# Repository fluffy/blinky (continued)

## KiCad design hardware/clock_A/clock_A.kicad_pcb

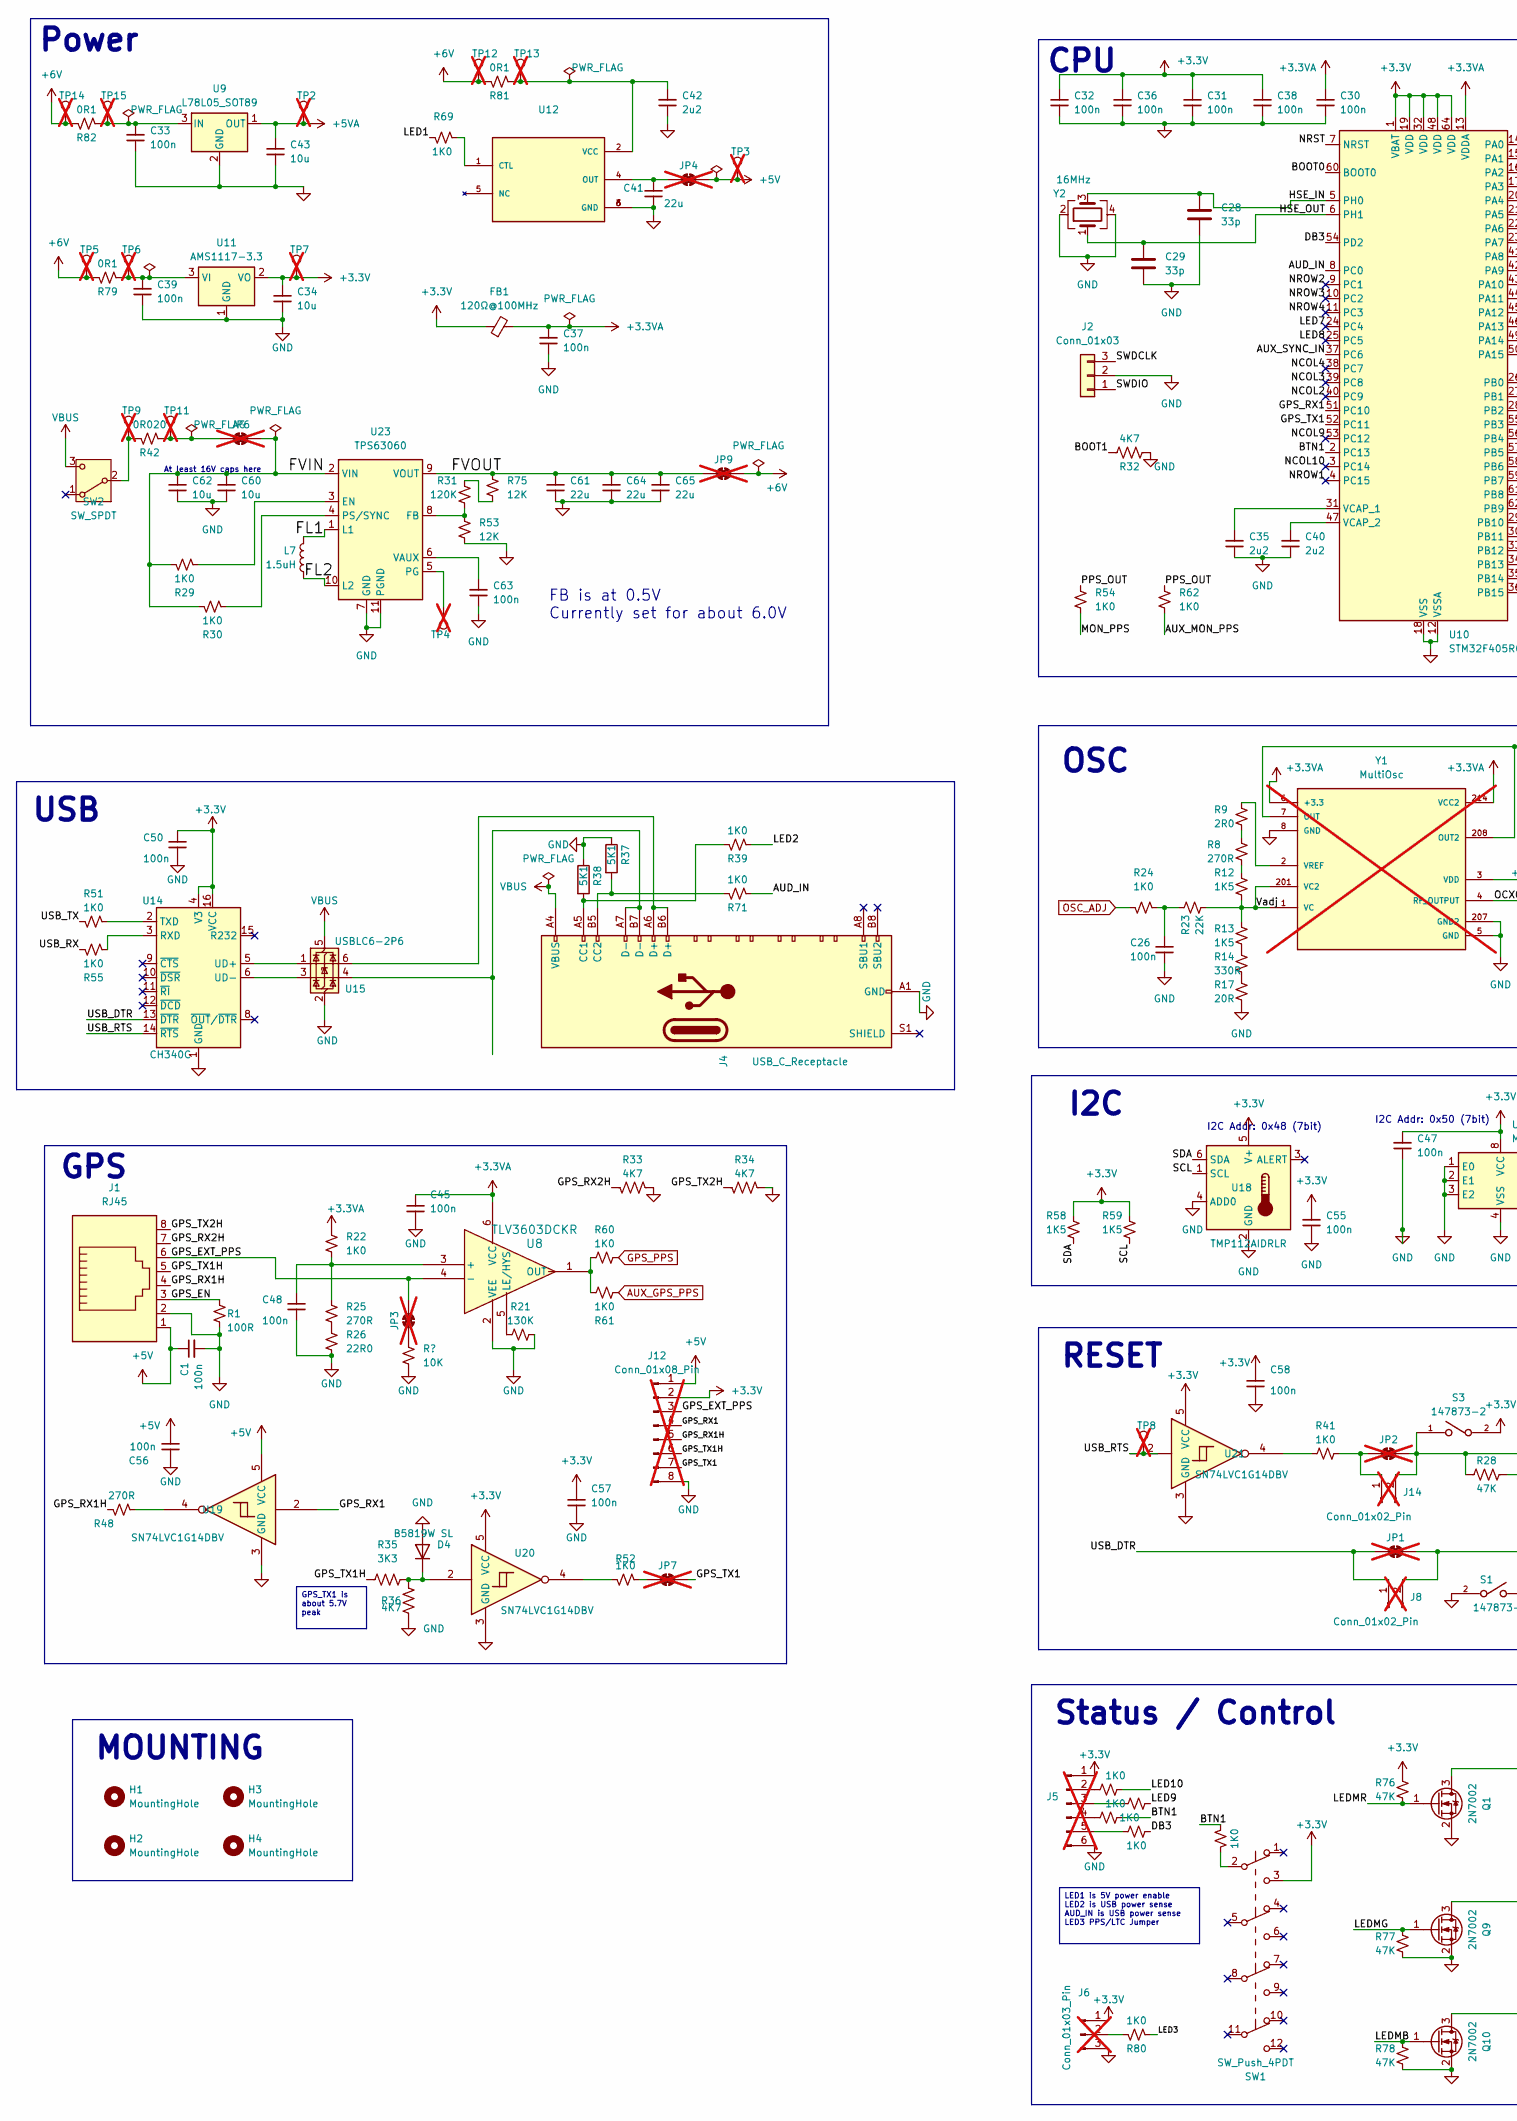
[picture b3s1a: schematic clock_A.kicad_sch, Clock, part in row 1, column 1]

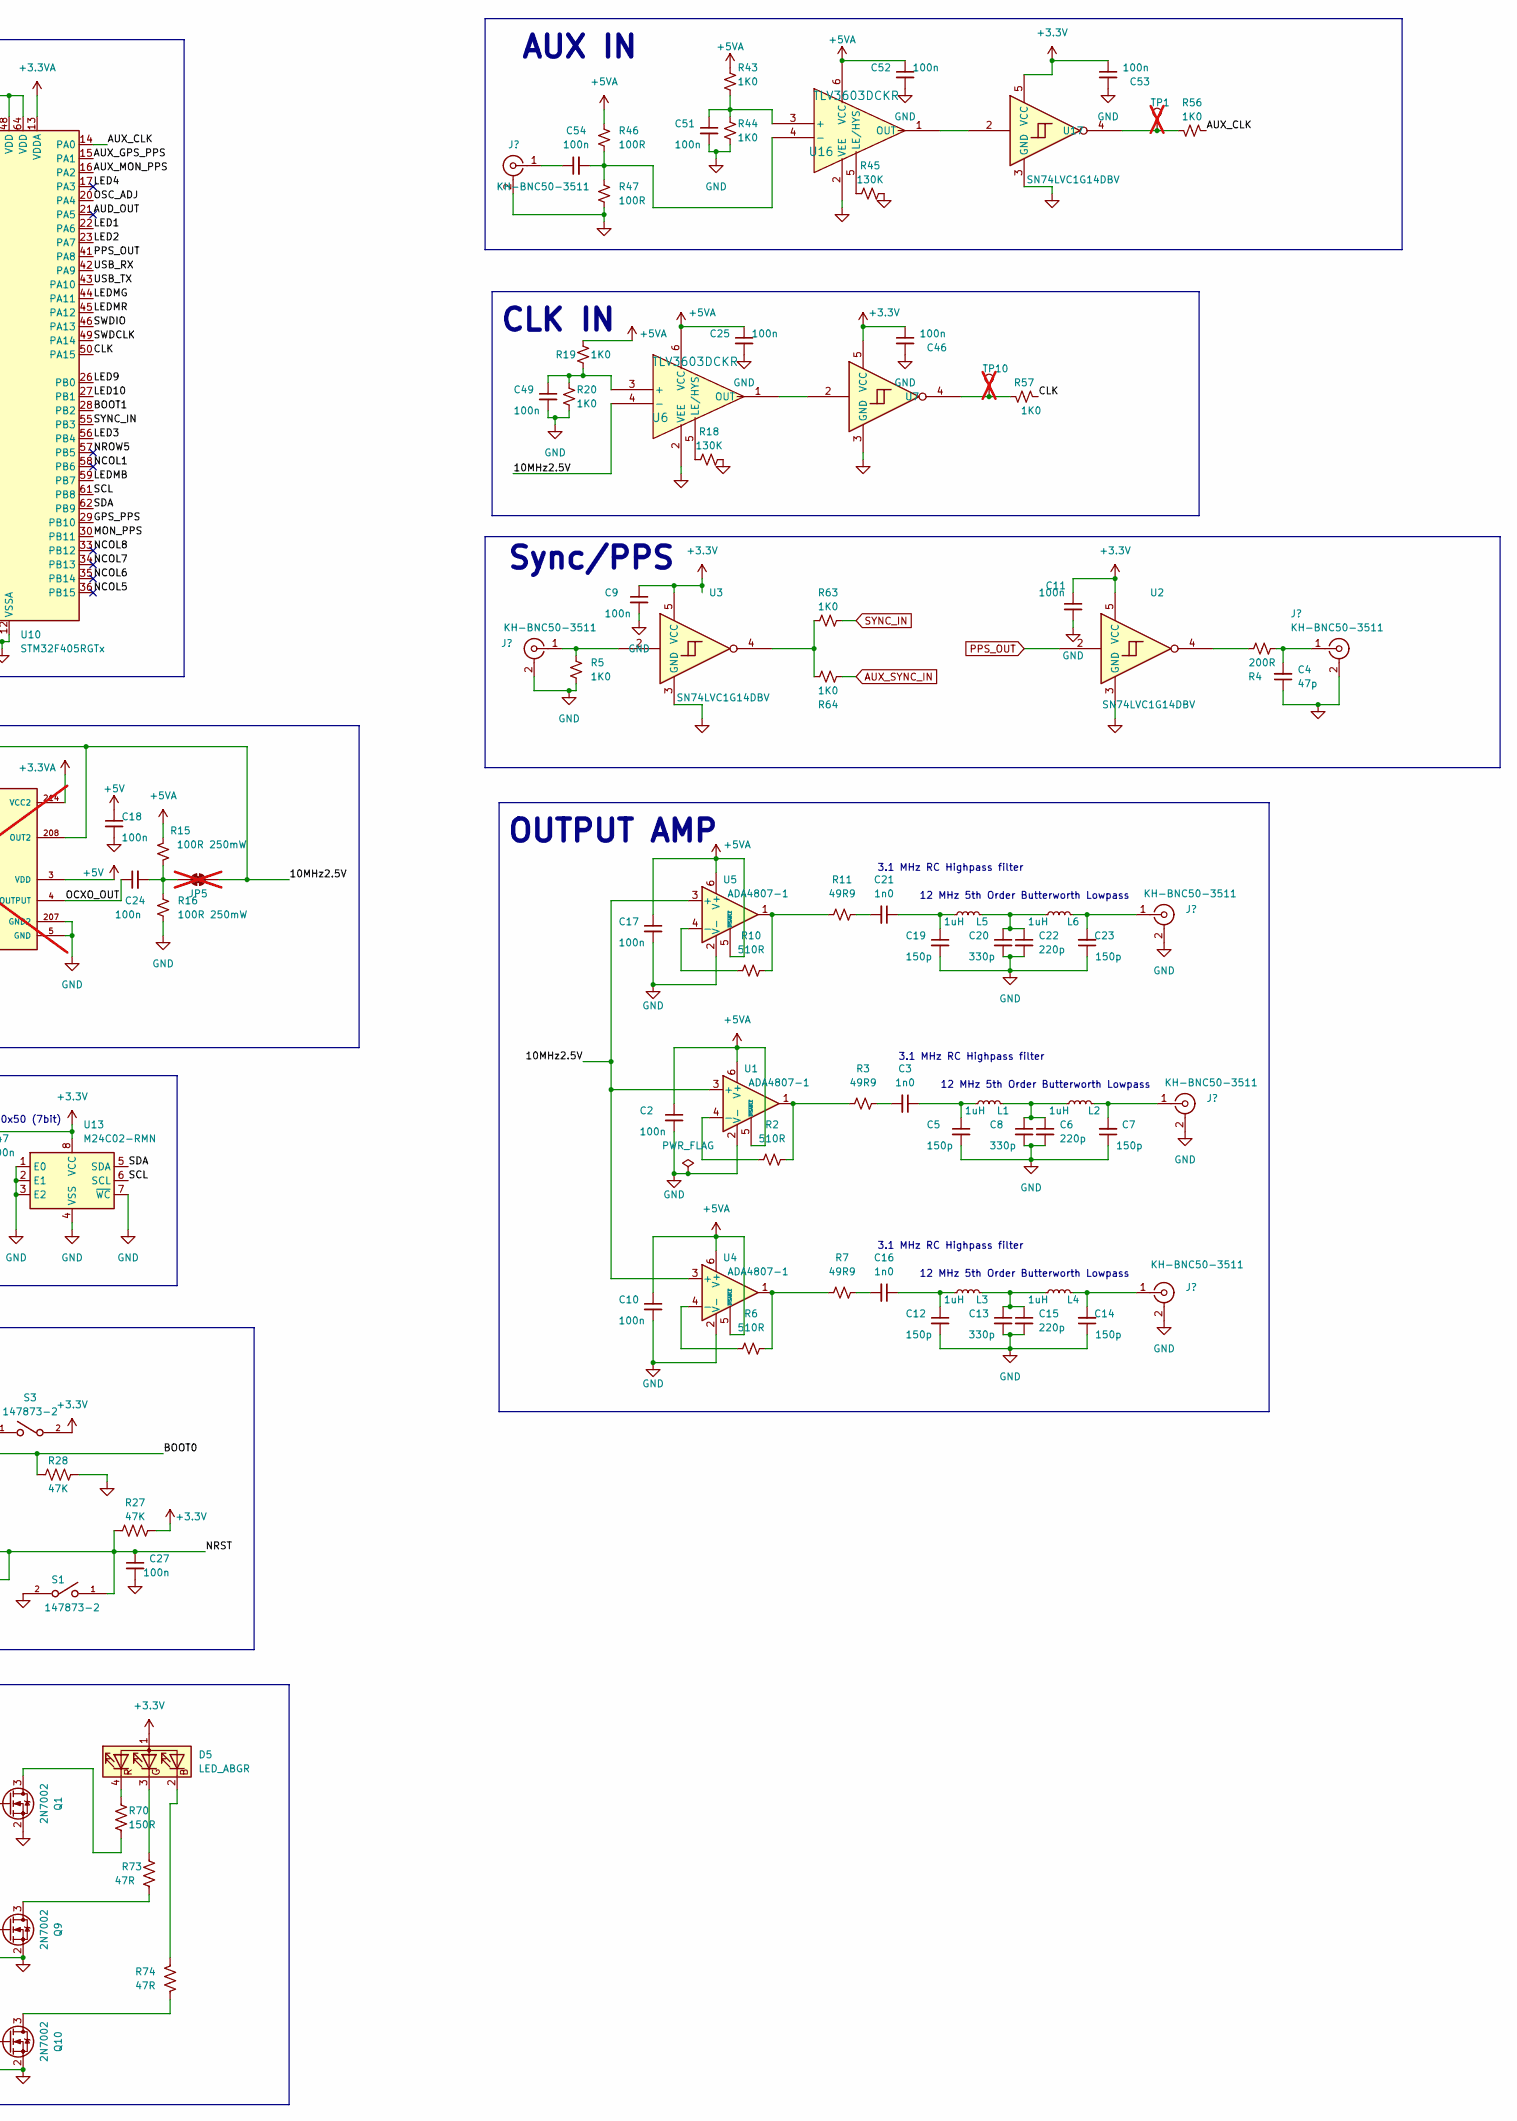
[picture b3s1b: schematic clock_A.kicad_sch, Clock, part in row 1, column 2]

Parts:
C1, C2, C9, C10, C11, C17, C18, C25, C26, C30, C31, C32, C33, C36, C38, C39, C45, C46, C47, C48, C49, C50, C51, C52, C53, C55, C56, C57, C58: 100n; C_0402_1005Metric; JLCPCB Part # C307331
C3, C16, C21: 1n0; C_0603_1608Metric; JLCPCB Part # C1588
C4: 47p; C_0603_1608Metric; JLCPCB Part # C1671
C5, C7, C12, C14, C19, C23: 150p; C_0603_1608Metric; JLCPCB Part # C1594
C6, C15, C22: 220p; C_0603_1608Metric; JLCPCB Part # C1603
C8, C13, C20: 330p; C_0603_1608Metric; JLCPCB Part # C1664
C24, C27, C37, C54, C63: 100n; C_0603_1608Metric; JLCPCB Part # C14663
C28, C29: 33p; C_0603_1608Metric; JLCPCB Part # C1663
C34, C43, C60, C62: 10u; C_0603_1608Metric; JLCPCB Part # C96446
C35, C40, C42: 2u2; C_0603_1608Metric; JLCPCB Part # C23630
C41, C61, C64, C65: 22u; C_0805_2012Metric; JLCPCB Part # C45783
D4: B5819W SL; D_SOD-123; JLCPCB Part # C8598
D5: LED_ABGR; LED_RGB_MHS110FRGBCT; MPN MHS110FRGBCT; JLCPCB Part # C496820
FB1: 120Ω@100MHz; R_0603_1608Metric; JLCPCB Part # C127301
H1, H2, H3, H4: MountingHole; MountingHole_2.2mm_M2
J1: RJ45; RJ45_Amphenol_RJHSE5380; JLCPCB Part # C464586
J2: Conn_01x03; JST_PH_S3B-PH-SM4-TB_1x03-1MP_P2.00mm_Horizontal; JLCPCB Part # C265101
J3, J7, J9, J10, J11, J13: KH-BNC50-3511; BNC_Amphenol_B6252HB-NPP3G-50_Horizontal-CJ; JLCPCB Part # C2837587
J4: USB_C_Receptacle; USB_C_Receptacle_HRO_TYPE-C-31-M-12; JLCPCB Part # C165948
J5: Conn_01x06_Pin; PinHeader_1x06_P2.54mm_Vertical; not fitted
J6: Conn_01x03_Pin; PinHeader_1x03_P2.54mm_Vertical; not fitted
J8, J14: Conn_01x02_Pin; PinHeader_1x02_P2.54mm_Vertical; not fitted
J12: Conn_01x08_Pin; PinHeader_1x08_P2.54mm_Vertical; not fitted
JP1, JP2, JP3, JP4, JP5, JP6, JP7, JP9: SolderJumper_2_Bridged; SolderJumper-2_P1.3mm_Bridged2Bar_RoundedPad1.0x1.5mm; not fitted
L1, L2, L3, L4, L5, L6: 1uH; L_0805_2012Metric; JLCPCB Part # C1042
L7: 1.5uH; L_Coilcraft_XAL4020-XXX; MPN XFL4020-152MEC; JLCPCB Part # C3033018
Q1, Q9, Q10: 2N7002; SOT-23; JLCPCB Part # C8545
R1, R46, R47: 100R; R_0603_1608Metric; JLCPCB Part # C22775
R2, R6, R10: 510R; R_0603_1608Metric; JLCPCB Part # C23193
R3, R7, R11: 49R9; R_0603_1608Metric; JLCPCB Part # C23185
R4: 200R; R_0603_1608Metric; JLCPCB Part # C8218
R5, R19, R20, R22, R24, R29, R30, R39, R41, R43, R44, R51, R52, R54, R55, R56, R57, R60, R61, R62, R63, R64, R65, R66, R67, R68, R69, R71, R72, R80: 1K0; R_0603_1608Metric; JLCPCB Part # C21190
R8, R25, R48: 270R; R_0603_1608Metric; JLCPCB Part # C22966
R9: 2R0; R_0603_1608Metric; JLCPCB Part # C22977
R12, R13, R58, R59: 1K5; R_0603_1608Metric; JLCPCB Part # C22843
R14: 330R; R_0603_1608Metric; JLCPCB Part # C23138
R15, R16: 100R 250mW; R_1206_3216Metric; JLCPCB Part # C17901
R17: 20R; R_0603_1608Metric; JLCPCB Part # C22950
R18, R21, R45: 130K; R_0603_1608Metric; JLCPCB Part # C22795
R23: 22K; R_0603_1608Metric; JLCPCB Part # C31850
R26: 22R0; R_0603_1608Metric; JLCPCB Part # C23345
R27, R28, R76, R77, R78: 47K; R_0603_1608Metric; JLCPCB Part # C25819
R31: 120K; R_0603_1608Metric; JLCPCB Part # C25808
R32, R33, R34, R36: 4K7; R_0603_1608Metric; JLCPCB Part # C23162
R35: 3K3; R_0603_1608Metric; JLCPCB Part # C22978
R37, R38: 5K1; R_0603_1608Metric; JLCPCB Part # C23186
R42: 0R020; R_1206_3216Metric; JLCPCB Part # C2765435
R50: 10K; R_0603_1608Metric; JLCPCB Part # C25804
R53, R75: 12K; R_0603_1608Metric; JLCPCB Part # C22790
R70: 150R; R_0603_1608Metric; JLCPCB Part # C22808
R73, R74: 47R; R_0603_1608Metric; JLCPCB Part # C23182
R79, R81, R82: 0R1; R_1206_3216Metric; JLCPCB Part # C25334
S1, S3: 147873-2; SW_147873-2; JLCPCB Part # C266189
SW1: SW_Push_4PDT; PBH4UOANAGX; JLCPCB Part # C273424
SW2: SW_SPDT; SW_E-Switch_EG1224_SPDT_Angled; JLCPCB Part # C273395
TP1, TP2, TP3, TP4, TP5, TP6, TP7, TP8, TP9, TP10, TP11, TP12, TP13, TP14, TP15: TestPoint_THTPad_D1.0mm_Drill0.5mm; not fitted
U1, U4, U5: ADA4807-1; SOT-23-6; JLCPCB Rotation Offset 90
U2, U3, U7, U17, U19, U20, U21: SN74LVC1G14DBV; SOT-23-5; JLCPCB Part # C133145
U6, U8, U16: TLV3603DCKR; SOT-363_SC-70-6; JLCPCB Part # C5213955
U9: L78L05_SOT89; SOT-89-3; JLCPCB Part # C71136
U10: STM32F405RGTx; LQFP-64_10x10mm_P0.5mm; JLCPCB Part # C15742
U11: AMS1117-3.3; SOT-223-3_TabPin2; JLCPCB Part # C6186
U12: BA50DD0WHFP-TR; DPAK172P1054X200-6N; PARTREV 003; JLCPCB Position Offset -1.5,0
U13: M24C02-RMN; SOIC-8_3.9x4.9mm_P1.27mm; JLCPCB Part # C83836
U14: CH340C; SOIC-16_3.9x9.9mm_P1.27mm; JLCPCB Part # C7464026
U15: USBLC6-2P6; SOT-666; JLCPCB Part # C2827693
U18: TMP112AIDRLR; SOT-563; JLCPCB Part # C28927
U23: TPS63060; Texas_S-PWSON-N10_ThermalVias-CJ; JLCPCB Part # C48567
Y1: MultiOsc; XTAL_Multi; not fitted
Y2: 16MHz; Crystal_SMD_3225-4Pin_3.2x2.5mm; JLCPCB Part # C13738

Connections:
+3.3V: C9.1, C11.1, C31.1, C32.1, C34.1, C36.1, C38.1, C46.1, C47.2, C50.1, C53.1, C55.2, C57.1, C58.1, D5.1 (A), FB1.1, J5.1, J6.1, J12.2, R27.1, R58.1, R59.1, R76.1, S3.2, SW1.3 (C), TP7.1, U2.5 (VCC), U3.5 (VCC), U7.5 (VCC), U10.1 (VBAT), U10.19 (VDD), U10.32 (VDD), U10.48 (VDD), U10.64 (VDD), U11.2 (VO), U13.8 (VCC), U14.4 (V3), U14.16 (VCC), U17.5 (VCC), U18.5 (V+), U20.5 (VCC), U21.5 (VCC)
+3.3VA: C30.1, C37.2, C45.1, FB1.2, R22.1, U8.6 (VCC), U10.13 (VDDA), Y1.6 (+3.3), Y1.214 (VCC2)
+5V: C1.1, C18.1, C56.1, J1.1, J12.1, JP4.2 (B), TP3.1, U19.5 (VCC), Y1.3 (VDD)
+5VA: C2.1, C10.1, C17.1, C25.1, C43.1, C52.1, R15.1, R19.1, R43.1, R46.1, TP2.1, U1.5 (~DISABLE), U1.6 (V+), U4.5 (~DISABLE), U4.6 (V+), U5.5 (~DISABLE), U5.6 (V+), U6.6 (VCC), U9.1 (OUT), U16.6 (VCC)
+6V: JP9.2 (B), R79.2, R81.2, R82.2, TP5.1, TP12.1, TP14.1
/10MHz2.5V: JP5.1 (A), U1.3 (+), U4.3 (+), U5.3 (+), U6.4 (-), Y1.7 (OUT), Y1.208 (OUT2)
/AUD_IN: R71.2, U10.8 (PC0)
/AUD_OUT: U10.21 (PA5)
/AUX_CLK: R56.1, U10.14 (PA0)
/AUX_MON_PPS: R62.2, U10.16 (PA2)
/BOOT0: J14.2, JP2.2 (B), R28.1, S3.1, U10.60 (BOOT0)
/BOOT1: R32.2, U10.28 (PB2)
/BTN1: R66.1, R72.2, U10.2 (PC13)
/CLK: R57.1, U10.50 (PA15)
/DB3: R68.1, U10.54 (PD2)
/FL1: L7.1, U23.1 (L1)
/FL2: L7.2, U23.10 (L2)
/FVIN: C60.1, C62.1, JP6.2 (B), R29.1, R30.1, U23.2 (VIN)
/FVOUT: C61.1, C64.1, C65.1, JP9.1 (A), R75.1, U23.9 (VOUT)
/GPS_EN: J1.3, R1.1
/GPS_EXT_PPS: J1.6, J12.3, JP3.2 (B), U8.4 (-)
/GPS_RX1: J12.4, U10.51 (PC10), U19.2
/GPS_RX1H: J1.4, J12.5, R48.2
/GPS_RX2H: J1.7, R33.2
/GPS_TX1: J12.7, JP7.2 (B), U10.52 (PC11)
/GPS_TX1H: J1.5, J12.6, R35.2
/GPS_TX2H: J1.8, R34.2
/HSE_IN: C28.1, U10.5 (PH0), Y2.3
/HSE_OUT: C29.1, U10.6 (PH1), Y2.1
/LED1: R69.2, U10.22 (PA6)
/LED2: R39.2, U10.23 (PA7)
/LED3: R80.1, U10.56 (PB4)
/LED4: U10.17 (PA3)
/LED7: U10.24 (PC4)
/LED8: U10.25 (PC5)
/LED9: R67.1, U10.26 (PB0)
/LED10: R65.1, U10.27 (PB1)
/LEDMB: Q10.1 (G), R78.1, U10.59 (PB7)
/LEDMG: Q9.1 (G), R77.1, U10.44 (PA11)
/LEDMR: Q1.1 (G), R76.2, U10.45 (PA12)
/MON_PPS: R54.2, U10.30 (PB11)
/NCOL1: U10.58 (PB6)
/NCOL2: U10.40 (PC9)
/NCOL3: U10.39 (PC8)
/NCOL4: U10.38 (PC7)
/NCOL5: U10.36 (PB15)
/NCOL6: U10.35 (PB14)
/NCOL7: U10.34 (PB13)
/NCOL8: U10.33 (PB12)
/NCOL9: U10.53 (PC12)
/NCOL10: U10.3 (PC14)
/NROW1: U10.4 (PC15)
/NROW2: U10.9 (PC1)
/NROW3: U10.10 (PC2)
/NROW4: U10.11 (PC3)
/NROW5: U10.57 (PB5)
/NRST: C27.1, J8.2, JP1.2 (B), R27.2, S1.1, U10.7 (NRST)
/OCXO_OUT: C24.1, Y1.4 (RF_OUTPUT)
/SCL: R59.2, U10.61 (PB8), U13.6 (SCL), U18.1 (SCL)
/SDA: R58.2, U10.62 (PB9), U13.5 (SDA), U18.6 (SDA)
/SWDCLK: J2.3, U10.49 (PA14)
/SWDIO: J2.1, U10.46 (PA13)
/USB_RTS: TP8.1, U14.14 (~RTS), U21.2
/USB_RX: R55.1, U10.42 (PA9)
/USB_TX: R51.2, U10.43 (PA10)
/Vadj: R12.2, R13.1, R23.2, Y1.1 (VC), Y1.201 (VC2)
AUX_GPS_PPS: R61.2, U10.15 (PA1)
AUX_SYNC_IN: R64.1, U10.37 (PC6)
GND: C1.2, C2.2, C4.1, C5.2, C6.2, C7.1, C8.2, C9.2, C10.2, C11.2, C12.2, C13.2, C14.1, C15.2, C17.2, C18.2, C19.2, C20.2, C22.2, C23.1, C25.2, C26.2, C27.2, C28.2, C29.2, C30.2, C31.2, C32.2, C33.1, C34.2, C35.1, C36.2, C37.1, C38.2, C39.1, C40.1, C41.2, C42.1, C43.2, C45.2, C46.2, C47.1, C48.2, C49.2, C50.2, C51.2, C52.2, C53.2, C55.1, C56.2, C57.2, C58.2, C60.2, C61.2, C62.2, C63.1, C64.2, C65.2, D4.2 (A), J1.2, J2.2, J3.2 (Ext), J4.A1 (GND), J4.A12 (GND), J4.B1 (GND), J4.B12 (GND), J5.6, J6.3, J7.2 (Ext), J9.2 (Ext), J10.2 (Ext), J11.2 (Ext), J12.8, J13.2 (Ext), Q1.2 (S), Q9.2 (S), Q10.2 (S), R1.2, R5.2, R16.2, R17.2, R18.2, R20.2, R21.2, R26.2, R28.2, R32.1, R33.1, R34.1, R36.1, R37.1, R38.1, R44.2, R45.2, R47.2, R50.2, R53.2, R77.2, R78.2, S1.2, U1.2 (V-), U2.3 (GND), U3.3 (GND), U4.2 (V-), U5.2 (V-), U6.2 (VEE), U7.3 (GND), U8.2 (VEE), U9.2 (GND), U10.12 (VSSA), U10.18 (VSS), U10.63 (VSS), U11.1 (GND), U12.3 (GND), U12.6 (GND), U13.1 (E0), U13.2 (E1), U13.3 (E2), U13.4 (VSS), U13.7 (~WC), U14.1 (GND), U15.2 (GND), U16.2 (VEE), U17.3 (GND), U18.2 (GND), U18.4 (ADD0), U19.3 (GND), U20.3 (GND), U21.3 (GND), U23.7 (GND), U23.11 (PGND), Y1.5 (GND), Y1.8 (GND), Y1.207 (GND2), Y2.2, Y2.4
GPS_PPS: R60.1, U10.29 (PB10)
unnamed: C3.1, C5.1, L1.1
unnamed: C3.2, R3.2
unnamed: C6.1, C8.1, L1.2, L2.2
unnamed: C12.1, C16.1, L3.1
unnamed: C13.1, C15.1, L3.2, L4.2
unnamed: C16.2, R7.2
unnamed: C19.1, C21.1, L5.1
unnamed: C20.1, C22.1, L5.2, L6.2
unnamed: C21.2, R11.2
unnamed: C26.1, R23.1, R24.1
unnamed: D4.1 (K), R35.1, R36.2, U20.2
unnamed: D5.2 (BK), R74.1
unnamed: D5.3 (GK), R73.2
unnamed: D5.4 (RK), R70.2
unnamed: C23.2, J3.1 (In), L6.1
unnamed: J4.A5 (CC1), R38.2, R39.1
unnamed: J4.B5 (CC2), R37.2, R71.1
unnamed: J4.A6 (D+), J4.B6 (D+), U15.6 (I/O1)
unnamed: J4.A7 (D-), J4.B7 (D-), U15.4 (I/O2)
unnamed: J5.2, R65.2
unnamed: J5.3, R67.2
unnamed: J5.4, R66.2
unnamed: J5.5, R68.2
unnamed: J6.2, R80.2
unnamed: C54.1, J7.1 (In)
unnamed: J9.1 (In), R5.1, U3.2
unnamed: C4.2, J10.1 (In), R4.2
unnamed: C14.2, J11.1 (In), L4.1
unnamed: C7.2, J13.1 (In), L2.1
unnamed: J14.1, JP2.1 (A), R41.2
unnamed: JP3.1 (A), R50.1
unnamed: C41.1, JP4.1 (A), U12.4 (OUT)
unnamed: C24.2, JP5.2 (B), R15.2, R16.1
unnamed: JP6.1 (A), R42.1, TP11.1
unnamed: JP7.1 (A), R52.1
unnamed: Q1.3 (D), R70.1
unnamed: Q9.3 (D), R73.1
unnamed: Q10.3 (D), R74.2
unnamed: R2.2, R3.1, U1.1
unnamed: R4.1, U2.4
unnamed: R6.2, R7.1, U4.1
unnamed: R8.1, R9.2
unnamed: R10.2, R11.1, U5.1
unnamed: R8.2, R12.1
unnamed: R13.2, R14.1
unnamed: R14.2, R17.1
unnamed: R25.2, R26.1
unnamed: R31.1, R75.2
unnamed: R41.1, U21.4
unnamed: R48.1, U19.4
unnamed: R52.2, U20.4
unnamed: R56.2, TP1.1, U17.4
unnamed: R57.2, TP10.1, U7.4
unnamed: R63.2, R64.2, U3.4
unnamed: R72.1, SW1.2 (B)
unnamed: R42.2, SW2.2 (B), TP9.1
unnamed: R2.1, U1.4 (-)
unnamed: R6.1, U4.4 (-)
unnamed: R10.1, U5.4 (-)
unnamed: C49.1, R19.2, R20.1, U6.3 (+)
unnamed: R18.1, U6.5 (LE/HYS)
unnamed: U6.1 (OUT), U7.2
unnamed: C48.1, R22.2, R25.1, U8.3 (+)
unnamed: R21.1, U8.5 (LE/HYS)
unnamed: R60.2, R61.1, U8.1 (OUT)
unnamed: C33.2, R82.1, TP15.1, U9.3 (IN)
unnamed: C35.2, U10.31 (VCAP_1)
unnamed: C40.2, U10.47 (VCAP_2)
unnamed: C39.2, R79.1, TP6.1, U11.3 (VI)
unnamed: R69.1, U12.1 (CTL)
unnamed: C42.2, R81.1, TP13.1, U12.2 (VCC)
unnamed: R55.2, U14.3 (RXD)
unnamed: R51.1, U14.2 (TXD)
unnamed: U14.5 (UD+), U15.1 (I/O1)
unnamed: U14.6 (UD-), U15.3 (I/O2)
unnamed: C51.1, R43.2, R44.1, U16.3 (+)
unnamed: C54.2, R46.2, R47.1, U16.4 (-)
unnamed: R45.1, U16.5 (LE/HYS)
unnamed: U16.1 (OUT), U17.2
unnamed: R29.2, U23.3 (EN)
unnamed: R31.2, R53.1, U23.8 (FB)
unnamed: TP4.1, U23.5 (PG)
unnamed: R30.2, U23.4 (PS/SYNC)
unnamed: C63.2, U23.6 (VAUX)
unnamed: R9.1, Y1.2 (VREF)
OSC_ADJ: R24.2, U10.20 (PA4)
PPS_OUT: R54.1, R62.1, U2.2, U10.41 (PA8)
SYNC_IN: R63.1, U10.55 (PB3)
VBUS: J4.A4 (VBUS), J4.A9 (VBUS), J4.B4 (VBUS), J4.B9 (VBUS), SW2.3 (C), U15.5 (VBUS)

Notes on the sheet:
LED1 is 5V power enable LED2 is USB power sense AUD_IN is USB power sense LED3 PPS/LTC Jumper
GPS_TX1 is about 5.7V peak
At least 16V caps here
AUX IN
RESET
OUTPUT AMP
USB
3.1 MHz RC Highpass filter
GPS
CPU
I2C
Status / Control
Sync/PPS
CLK IN
MOUNTING
12 MHz 5th Order Butterworth Lowpass
FB is at 0.5V Currently set for about 6.0V
I2C Addr: 0x48 (7bit)
I2C Addr: 0x50 (7bit)
OSC
Power

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
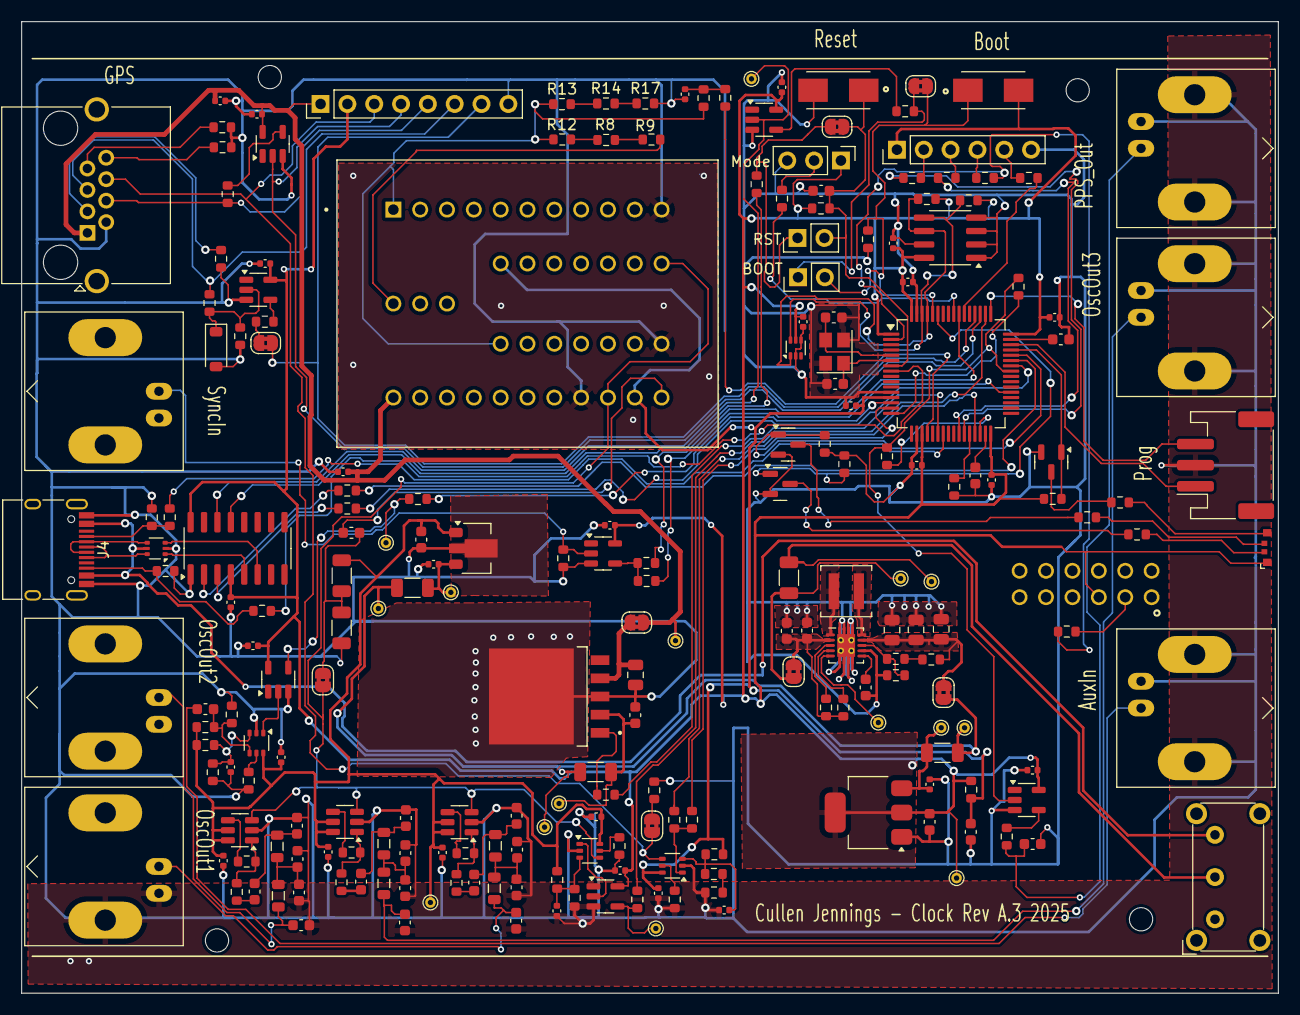
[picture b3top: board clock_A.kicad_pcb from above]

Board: 2 copper layers, 119.0 x 92.0 mm, 226 parts (0 on the bottom side), 142 nets.

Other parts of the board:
R40: 1K0; R_0603_1608Metric

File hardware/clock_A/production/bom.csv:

Designator,Footprint,Quantity,Value,LCSC Part #
"C1, C10, C11, C17, C18, C2, C25, C26, C30, C31, C32, C33, C36, C38, C39, C45, C46, C47, C48, C49, C50, C51, C52, C53, C55, C56, C57, C58, C9",0402,29,100n,C307331
"C12, C14, C19, C23, C5, C7",0603,6,150p,C1594
"C13, C20, C8",0603,3,330p,C1664
"C15, C22, C6",0603,3,220p,C1603
"C16, C21, C3",0603,3,1n0,C1588
"C24, C27, C37, C54, C63",0603,5,100n,C14663
"C28, C29",0603,2,33p,C1663
"C34, C43, C60, C62",0603,4,10u,C96446
"C35, C40, C42",0603,3,2u2,C23630
C4,0603,1,47p,C1671
"C41, C61, C64, C65",0805,4,22u,C45783
D4,D_SOD-123,1,B5819W SL,C8598
D5,LED_RGB_MHS110FRGBCT,1,LED_ABGR,C496820
FB1,0603,1,120Ω@100MHz ,C127301
J1,RJ45_Amphenol_RJHSE5380,1,RJ45,C464586
"J10, J11, J13, J3, J7, J9",BNC_Amphenol_B6252HB-NPP3G-50_Horizontal-CJ,6,KH-BNC50-3511,C2837587
J2,JST_PH_S3B-PH-SM4-TB_1x03-1MP_P2.00mm_Horizontal,1,Conn_01x03,C265101
J4,USB_C_Receptacle_HRO_TYPE-C-31-M-12,1,USB_C_Receptacle,C165948
"L1, L2, L3, L4, L5, L6",0805,6,1uH,C1042
L7,L_Coilcraft_XAL4020-XXX,1,1.5uH,C3033018
"Q1, Q10, Q9",SOT-23,3,2N7002,C8545
"R1, R46, R47",0603,3,100R,C22775
"R10, R2, R6",0603,3,510R,C23193
"R11, R3, R7",0603,3,49R9,C23185
"R12, R13, R58, R59",0603,4,1K5,C22843
R14,0603,1,330R,C23138
"R15, R16",1206,2,100R 250mW,C17901
R17,0603,1,20R,C22950
"R18, R21, R45",0603,3,130K,C22795
"R19, R20, R22, R24, R29, R30, R39, R41, R43, R44, R5, R51, R52, R54, R55, R56, R57, R60, R61, R62, R63, R64, R65, R66, R67, R68, R69, R71, R72, R80",0603,30,1K0,C21190
R23,0603,1,22K,C31850
"R25, R48, R8",0603,3,270R,C22966
R26,0603,1,22R0,C23345
"R27, R28, R76, R77, R78",0603,5,47K,C25819
R31,0603,1,120K,C25808
"R32, R33, R34, R36",0603,4,4K7,C23162
R35,0603,1,3K3,C22978
"R37, R38",0603,2,5K1,C23186
R4,0603,1,200R,C8218
R42,1206,1,0R020,C2765435
R50,0603,1,10K,C25804
"R53, R75",0603,2,12K,C22790
R70,0603,1,150R,C22808
"R73, R74",0603,2,47R,C23182
"R79, R81, R82",1206,3,0R1,C25334
R9,0603,1,2R0,C22977
"S1, S3",SW_147873-2,2,147873-2,C266189
SW1,PBH4UOANAGX,1,SW_Push_4PDT,C273424
SW2,SW_E-Switch_EG1224_SPDT_Angled,1,SW_SPDT,C273395
"U1, U4, U5",SOT-23-6,3,ADA4807-1,C2058411
U10,LQFP-64_10x10mm_P0.5mm,1,STM32F405RGTx,C15742
U11,SOT-223-3_TabPin2,1,AMS1117-3.3,C6186
U12,DPAK172P1054X200-6N,1,BA50DD0WHFP-TR,C509718
U13,SOIC-8_3.9x4.9mm_P1.27mm,1,M24C02-RMN,C83836
U14,SOIC-16_3.9x9.9mm_P1.27mm,1,CH340C,C7464026
U15,SOT-666,1,USBLC6-2P6,C2827693
"U16, U6, U8",SOT-363_SC-70-6,3,TLV3603DCKR,C5213955
"U17, U19, U2, U20, U21, U3, U7",SOT-23-5,7,SN74LVC1G14DBV,C133145
U18,SOT-563,1,TMP112AIDRLR,C28927
U23,Texas_S-PWSON-N10_ThermalVias-CJ,1,TPS63060,C48567
U9,SOT-89-3,1,L78L05_SOT89,C71136
Y2,Crystal_SMD_3225-4Pin_3.2x2.5mm,1,16MHz ,C13738

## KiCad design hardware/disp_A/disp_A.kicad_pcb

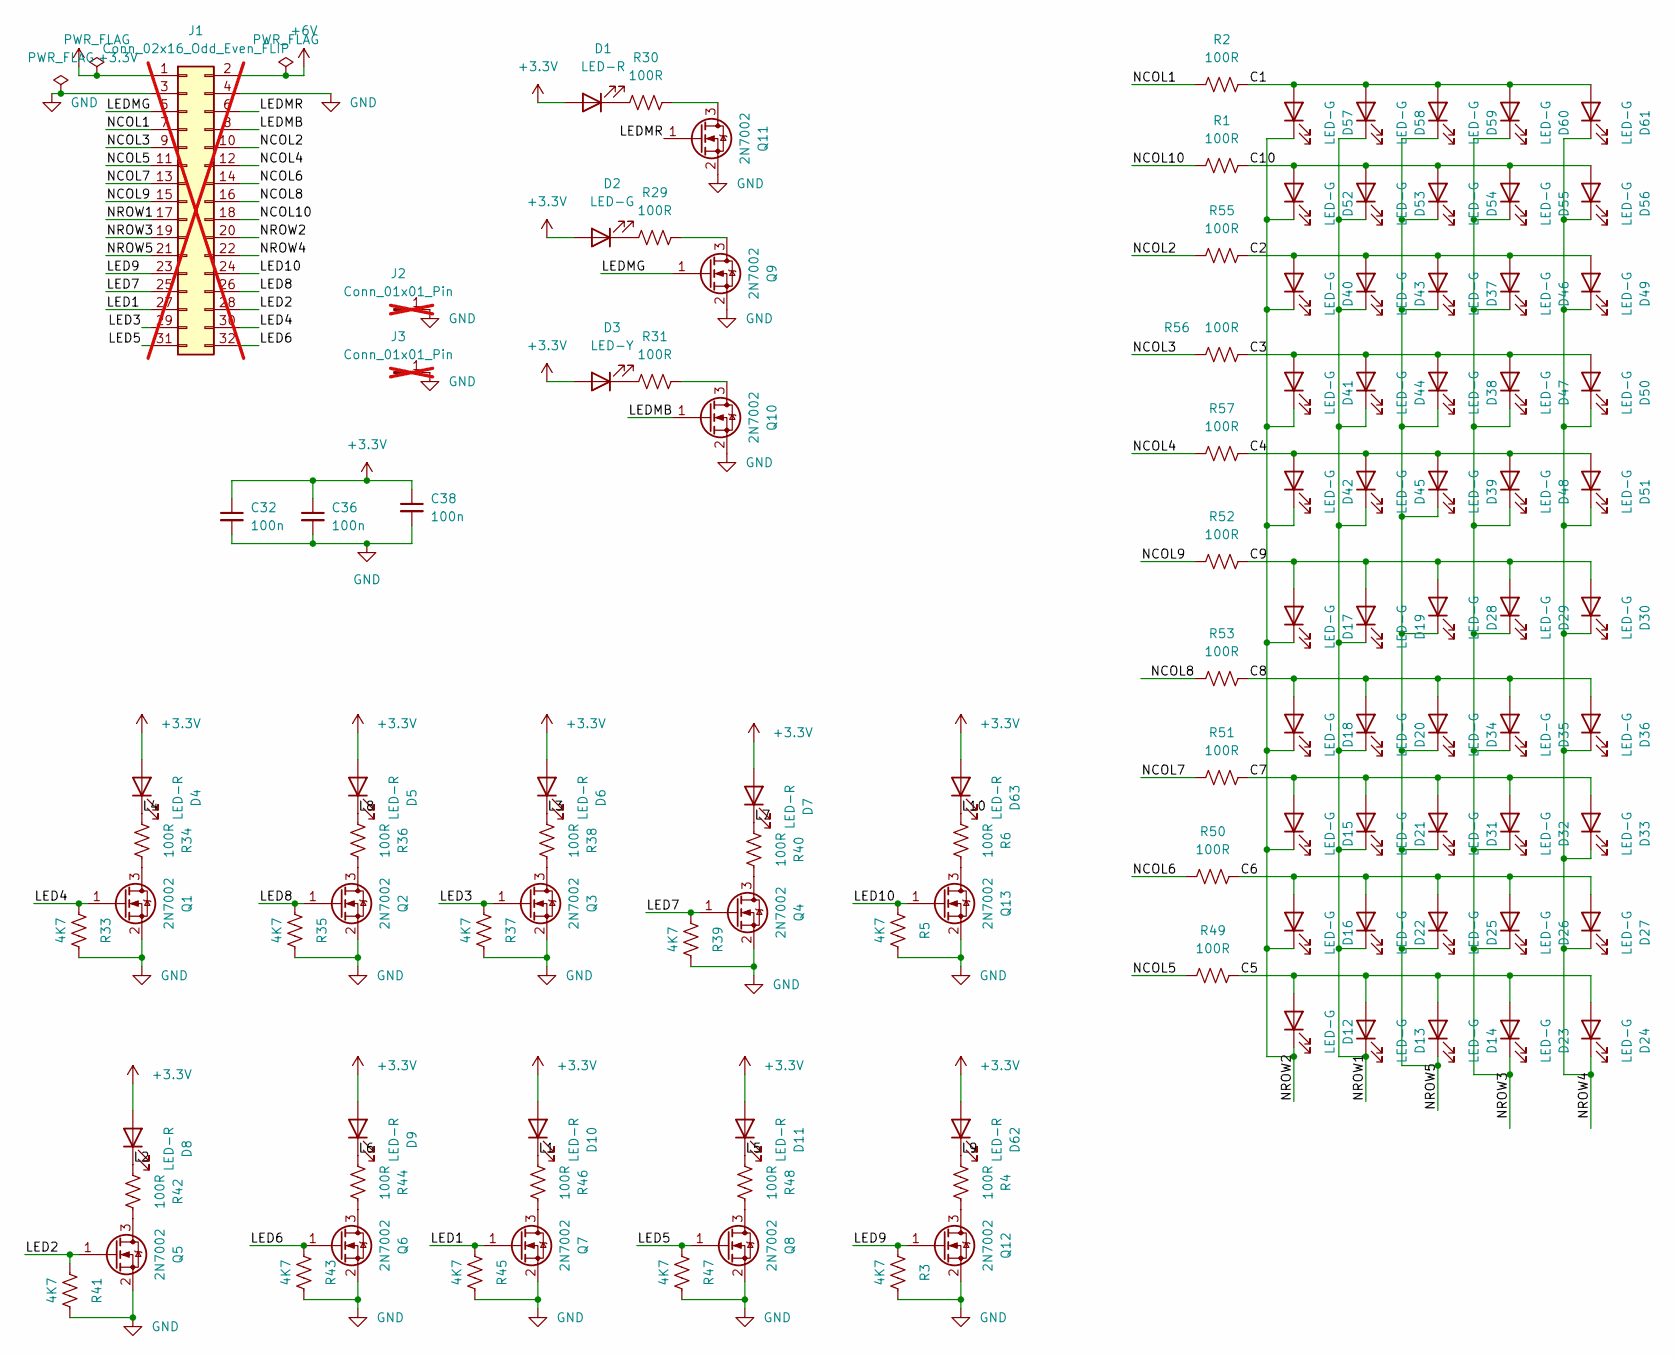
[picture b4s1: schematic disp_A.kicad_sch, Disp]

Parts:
C32, C36, C38: 100n; C_0402_1005Metric; JLCPCB Part # C307331
D1, D4, D5, D6, D7, D8, D9, D10, D11, D62, D63: LED-R; LED_0603_1608Metric; JLCPCB Part # C94869
D2, D12, D13, D14, D15, D16, D17, D18, D19, D20, D21, D22, D23, D24, D25, D26, D27, D28, D29, D30, D31, D32, D33, D34, D35, D36, D37, D38, D39, D40, D41, D42, D43, D44, D45, D46, D47, D48, D49, D50, D51, D52, D53, D54, D55, D56, D57, D58, D59, D60, D61: LED-G; LED_0603_1608Metric; JLCPCB Part # C125093
D3: LED-Y; LED_0603_1608Metric; JLCPCB Part # C72038
J1: Conn_02x16_Odd_Even_FLIP; PinHeader_2x16_P2.54mm_Vertical; not fitted
J2, J3: Conn_01x01_Pin; PinHeader_1x01_P2.54mm_Vertical; not fitted
Q1, Q2, Q3, Q4, Q5, Q6, Q7, Q8, Q9, Q10, Q11, Q12, Q13: 2N7002; SOT-23; JLCPCB Part # C8545
R1, R2, R4, R6, R29, R30, R31, R34, R36, R38, R40, R42, R44, R46, R48, R49, R50, R51, R52, R53, R55, R56, R57: 100R; R_0603_1608Metric; JLCPCB Part # C22775
R3, R5, R33, R35, R37, R39, R41, R43, R45, R47: 4K7; R_0603_1608Metric; JLCPCB Part # C23162

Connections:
+3.3V: C32.1, C36.1, C38.1, D1.2 (A), D2.2 (A), D3.2 (A), D4.2 (A), D5.2 (A), D6.2 (A), D7.2 (A), D8.2 (A), D9.2 (A), D10.2 (A), D11.2 (A), D62.2 (A), D63.2 (A), J1.1
+6V: J1.2
/C1: D57.2 (A), D58.2 (A), D59.2 (A), D60.2 (A), D61.2 (A), R2.1
/C2: D37.2 (A), D40.2 (A), D43.2 (A), D46.2 (A), D49.2 (A), R55.1
/C3: D38.2 (A), D41.2 (A), D44.2 (A), D47.2 (A), D50.2 (A), R56.1
/C4: D39.2 (A), D42.2 (A), D45.2 (A), D48.2 (A), D51.2 (A), R57.1
/C5: D12.2 (A), D13.2 (A), D14.2 (A), D23.2 (A), D24.2 (A), R49.1
/C6: D16.2 (A), D22.2 (A), D25.2 (A), D26.2 (A), D27.2 (A), R50.1
/C7: D15.2 (A), D21.2 (A), D31.2 (A), D32.2 (A), D33.2 (A), R51.1
/C8: D18.2 (A), D20.2 (A), D34.2 (A), D35.2 (A), D36.2 (A), R53.1
/C9: D17.2 (A), D19.2 (A), D28.2 (A), D29.2 (A), D30.2 (A), R52.1
/C10: D52.2 (A), D53.2 (A), D54.2 (A), D55.2 (A), D56.2 (A), R1.1
/L1: D10.1 (K), R46.1
/L2: D8.1 (K), R42.1
/L3: D6.1 (K), R38.1
/L4: D4.1 (K), R34.1
/L5: D11.1 (K), R48.1
/L6: D9.1 (K), R44.1
/L7: D7.1 (K), R40.1
/L8: D5.1 (K), R36.1
/L9: D62.1 (K), R4.1
/L10: D63.1 (K), R6.1
/LED1: J1.27, Q7.1 (G), R45.2
/LED2: J1.28, Q5.1 (G), R41.2
/LED3: J1.29, Q3.1 (G), R37.2
/LED4: J1.30, Q1.1 (G), R33.2
/LED5: J1.31, Q8.1 (G), R47.2
/LED6: J1.32, Q6.1 (G), R43.2
/LED7: J1.25, Q4.1 (G), R39.2
/LED8: J1.26, Q2.1 (G), R35.2
/LED9: J1.23, Q12.1 (G), R3.2
/LED10: J1.24, Q13.1 (G), R5.2
/LEDMB: J1.8, Q10.1 (G)
/LEDMG: J1.5, Q9.1 (G)
/LEDMR: J1.6, Q11.1 (G)
/NCOL1: J1.7, R2.2
/NCOL2: J1.10, R55.2
/NCOL3: J1.9, R56.2
/NCOL4: J1.12, R57.2
/NCOL5: J1.11, R49.2
/NCOL6: J1.14, R50.2
/NCOL7: J1.13, R51.2
/NCOL8: J1.16, R53.2
/NCOL9: J1.15, R52.2
/NCOL10: J1.18, R1.2
/NROW1: D13.1 (K), D19.1 (K), D20.1 (K), D21.1 (K), D22.1 (K), D43.1 (K), D44.1 (K), D45.1 (K), D53.1 (K), D58.1 (K), J1.17
/NROW2: D12.1 (K), D15.1 (K), D16.1 (K), D17.1 (K), D18.1 (K), D40.1 (K), D41.1 (K), D42.1 (K), D52.1 (K), D57.1 (K), J1.20
/NROW3: D23.1 (K), D26.1 (K), D29.1 (K), D32.1 (K), D35.1 (K), D46.1 (K), D47.1 (K), D48.1 (K), D55.1 (K), D60.1 (K), J1.19
/NROW4: D24.1 (K), D27.1 (K), D30.1 (K), D33.1 (K), D36.1 (K), D49.1 (K), D50.1 (K), D51.1 (K), D56.1 (K), D61.1 (K), J1.22
/NROW5: D14.1 (K), D25.1 (K), D28.1 (K), D31.1 (K), D34.1 (K), D37.1 (K), D38.1 (K), D39.1 (K), D54.1 (K), D59.1 (K), J1.21
GND: C32.2, C36.2, C38.2, J1.3, J1.4, J2.1, J3.1, Q1.2 (S), Q2.2 (S), Q3.2 (S), Q4.2 (S), Q5.2 (S), Q6.2 (S), Q7.2 (S), Q8.2 (S), Q9.2 (S), Q10.2 (S), Q11.2 (S), Q12.2 (S), Q13.2 (S), R3.1, R5.1, R33.1, R35.1, R37.1, R39.1, R41.1, R43.1, R45.1, R47.1
unnamed: D1.1 (K), R30.1
unnamed: D2.1 (K), R29.1
unnamed: D3.1 (K), R31.1
unnamed: Q1.3 (D), R34.2
unnamed: Q2.3 (D), R36.2
unnamed: Q3.3 (D), R38.2
unnamed: Q4.3 (D), R40.2
unnamed: Q5.3 (D), R42.2
unnamed: Q6.3 (D), R44.2
unnamed: Q7.3 (D), R46.2
unnamed: Q8.3 (D), R48.2
unnamed: Q9.3 (D), R29.2
unnamed: Q10.3 (D), R31.2
unnamed: Q11.3 (D), R30.2
unnamed: Q12.3 (D), R4.2
unnamed: Q13.3 (D), R6.2
